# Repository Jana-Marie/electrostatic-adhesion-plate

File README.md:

# electrostatic-adhesion-plate

#### Motivation

The motivation behind this project is that I wanted to test how strong [electro-adhesion](https://en.wikipedia.org/wiki/Electroadhesion) really is and what clamping force I can get myself with it. Since PCBs are very inexpensive nowadays, the choice fell on electrodes directly on a circuit board. In the first version (100x100mm) the electrode gap is not yet optimal and there are points where corona discharges are likely, this is fixed in the second version (DinA5).

A batch (50pcs) of the seccond version is about to be ordered by me.

#### Design

The boards were designed so that they can be connected to larger printed circuit boards (electrically) using solder connections. This makes it possible to build relatively large electroadhesive surfaces with relatively inexpensive printed circuit boards.

The surface of each PCB or the whole panel should be coated with a high voltage isolator, as the soldermask does not withstand high voltage very well. Kapton is a suitable material as its dielectric strength is about 7.6kV/25µm, unfortunately it is difficult to apply.
Another solution which is being tested is PlastiDip. PlastiDip has a much lower dielectric strength 1.6kV/25µm, so it has to be applied thicker. The advantage here is the rubber-like surface which generates a higher shear force due to its friction.

https://github.com/user-attachments/assets/e9a8f286-f70a-4371-af7a-df20809293cf

https://github.com/user-attachments/assets/fc1b60f5-51d2-4803-b8a3-286581b4381b

The electrode voltage should be between 500V and 5kV DC (depending on the design), whereby a higher voltage means a higher holding force. This voltage can be obtained from any cheap DC high voltage source (e.g. a bug zapper) or from a low AC voltage source (Please do not use direct mains voltage). The AC voltage can be multiplied and rectified by the Cockcroft Walton voltage multiplier on the back of the PCB.

___

## [100mm * 100mm](100100mm/)

| **Parameter**         | **Value**         |
| -------------     |:-------------:|
| Electrode Voltage | 500V-2000V    |
| Electrode Voltage*| 500V-3000V    |
| *Without extra coating (silkscreen)*|
| shearing force    | 9N @1.4kV     |
| shearing force cm²| 90mN/cm² @1.2kV|
| adhesive force    | **            |
| **PlastiDip Coating**                 |
| shearing force    | 4N @1.4kV     |
| shearing force cm²| 40mN/cm² @1.2kV|
| adhesive force    | **            |
| **Kapton Coating**                 |
| shearing force    | 2.5N @1.4kV     |
| shearing force cm²| 25mN/cm² @1.2kV|
| adhesive force    | **            |

\* With Insulation

\** TBD

#### [Demo Video](https://twitter.com/_Jana_Marie/status/1094664006059593729)

___

## [DIN A5](DINA5)

| **Parameter**         | **Value**         |
| -------------     |:-------------:|
| Electrode Voltage | 500V-2000V    |
| Electrode Voltage*| 500V-5000V    |
| shearing force    | **            |
| adhesive force    | **            |

\* With Insulation

\** TBD

#### Changes to V1 (100100mm)

 * Size is now 148*210mm (DinA5)
 * Electrode width and distance are optimized
 * M3 threads where added
 * Sharp edges where removed

### [5050mm](DINA5)

| **Parameter**         | **Value**         |
| -------------     |:-------------:|
| Electrode Voltage | 500V-2000V    |
| Electrode Voltage*| 500V-5000V    |
| shearing force    | 600mN         |
| shearing force cm²| 6mN/cm² @1.2kV|
| adhesive force    | **            |

\* With Insulation

\** TBD

### License

Copyright Jana Marie Hemsing 2022.

This source describes Open Hardware and is licensed under the CERN-OHL-S v2.

You may redistribute and modify this source and make products using it under
the terms of the CERN-OHL-S v2 (https://ohwr.org/cern_ohl_s_v2.txt).

This source is distributed WITHOUT ANY EXPRESS OR IMPLIED WARRANTY,
INCLUDING OF MERCHANTABILITY, SATISFACTORY QUALITY AND FITNESS FOR A
PARTICULAR PURPOSE. Please see the CERN-OHL-S v2 for applicable conditions.

Source location: https://github.com/Jana-Marie/electrostatic-adhesion-plate

As per CERN-OHL-S v2 section 4, should You produce hardware based on this
source, You must where practicable maintain the Source Location visible
on the external case of the Gizmo or other products you make using this
source.

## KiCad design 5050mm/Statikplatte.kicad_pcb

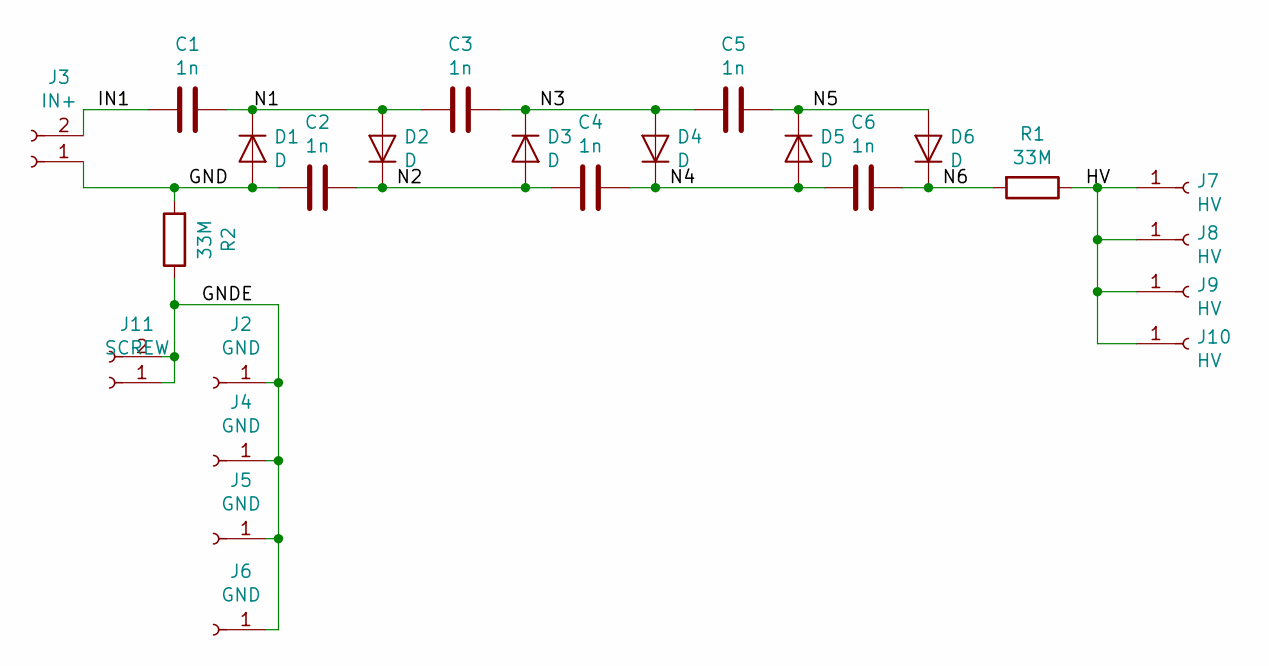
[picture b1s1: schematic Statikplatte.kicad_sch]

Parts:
C1, C2, C3, C4, C5, C6: 1n; C_1812_4532Metric
D1, D2, D3, D4, D5, D6: D; SMAF
J2, J4, J5, J6: GND; TestPoint_Pad_4.0x4.0mm
J3: IN+; LED_Connector
J7, J8, J9, J10: HV; TestPoint_Pad_4.0x4.0mm
J11: SCREW; M3_Screw
R1, R2: 33M; R_2512_6332Metric

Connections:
/GND: C2.2, D1.2 (A), J3.1, R2.2
/GNDE: J2.1, J4.1, J5.1, J6.1, J11.1, J11.2, R2.1
/HV: J7.1, J8.1, J9.1, J10.1, R1.1
/IN1: C1.2, J3.2
/N1: C1.1, C3.2, D1.1 (K), D2.2 (A)
/N2: C2.1, C4.2, D2.1 (K), D3.2 (A)
/N3: C3.1, C5.2, D3.1 (K), D4.2 (A)
/N4: C4.1, C6.2, D4.1 (K), D5.2 (A)
/N5: C5.1, D5.1 (K), D6.2 (A)
/N6: C6.1, D6.1 (K), R1.2

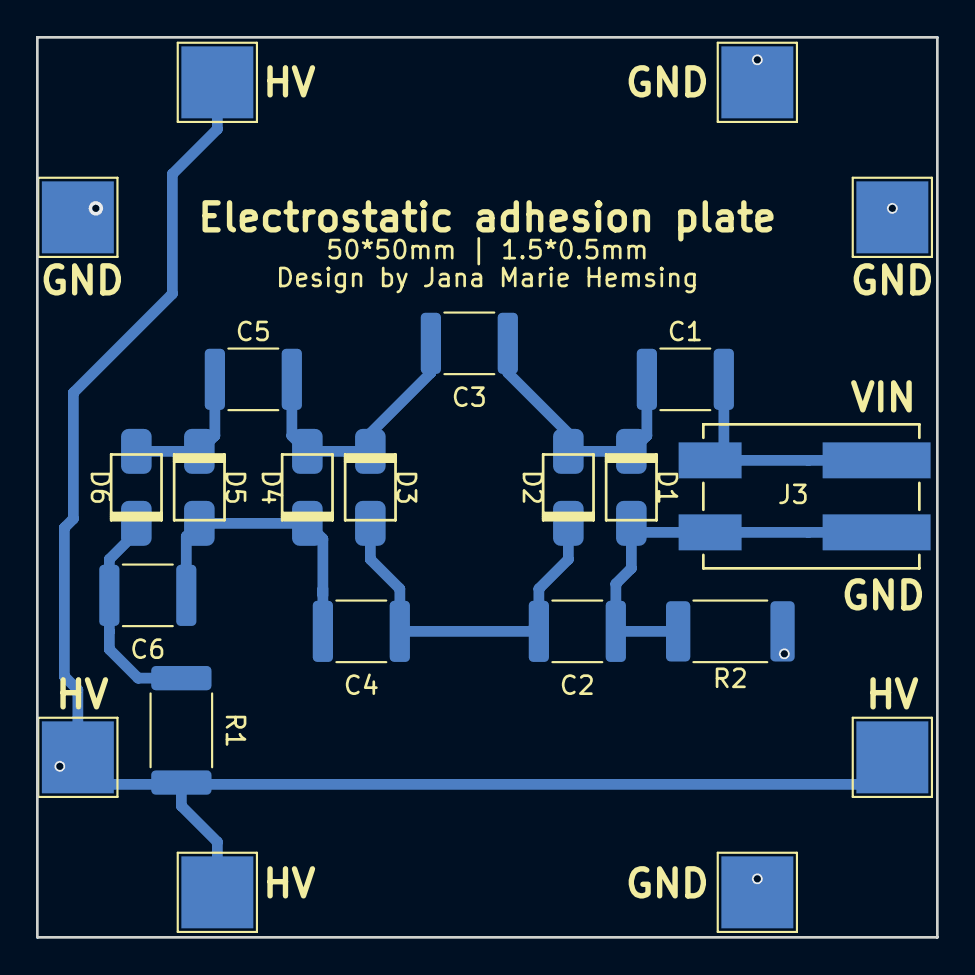
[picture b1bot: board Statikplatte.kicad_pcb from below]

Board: 4 copper layers, 50.0 x 50.0 mm, 23 parts (23 on the bottom side), 10 nets.

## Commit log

2019-01-23 added KiCAD files
2019-01-23 added images
2019-01-23 added gerber
2019-02-11 moved files and created DINA5 sized adhesion plate
2019-02-11 added DINA5 files
2019-02-11 fixed READMES
2019-02-11 removed double folders
2019-02-11 added README
2019-02-11 added screws
2019-02-11 updated schematic
2019-02-12 updated PCB
2019-02-12 updated images
2019-02-12 removed old image
2019-02-12 added Otter
2019-02-12 changed links to relative
2019-02-12 moved screws and added contributor
2019-02-12 Create LICENSE
2019-02-13 added resistor to gnd
2019-02-18 added image
2019-02-22 added negative kaskade
2019-02-22 updated image
2019-02-24 went back to one voltage multiplier
2019-02-24 updated PCB and Gerber
2019-02-25 added 50*50mm 4 layer test pcb
2021-10-04 updated design
2021-10-04 updated boards
2022-01-09 updated to KICAD 6
